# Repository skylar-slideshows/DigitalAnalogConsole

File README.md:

Skylar - Digital/Analog Music Mixing Console / Gear
A music mixing console with a fully analog audio signal path (no DSP), managed by a digital control system.

The problem to fix
Historically, music recording studios relied on analog audio processing equipment. While digital signal processing has largely replaced it, many professional audio engineers still prefer analog hardware for its perceived superior sound quality. However, analog equipment lacks instant recall, requiring engineers to manually reset knobs and controls between projects. Since these knobs control actual resistances/potentiometers in the signal path, they need to be physically moved to the right place. In today's fast-paced production environment, where multiple sessions may be completed in a single day, this process can be time-consuming and impractical.

Proposal
My proposal is to design a set of basic audio engineering analog sound processors (an EQualizer, a dynamic range compressor, and volume control) with a digital system that uses “voltage controlled resistors” to allow recall to be handled by a microprocessor, making it instant. Instead of having moving knobs that are physical resistors, the knobs will only be digital rotary encoders for which a microcontroller calculates their relative position. The microcontroller then uses a control voltage to set resistors in the analog signal path to the value that a real knob in that position would be, making the signal path exactly the same “to the audio.” This would also allow the microprocessor to automate and adjust many parameters at once, which is another limitation with analog audio equipment. These three basic devices can be combined into one digitally controlled, analog “channel strip” that handles one layer of audio in the mix of a song. Many of these channels side by side, with a master section that combines all the signals, makes an audio console. This kind of technology is present in some standalone pieces of audio equipment, as well as parts of some synthesizers, but it has never been done at such a large scale.

Technical explanation
The “knobs” in our device (actually rotary encoders), send a digital signal with their relative position. To “scan” all the digital encoder “knobs” positions’, a microcontroller can be multiplexed to them, cycling through looking at all the knobs’ data outputs several times per second, meaning a few GPIO pins can be used to interface with many knobs. 

The microcontroller then calculates the value that a real potentiometer (based on its value and taper - linear? Log? anti-log?) would have in that same positon.

To make voltage controlled resistors that actually supply this resistance in the analog audio path, there are many approaches. A FET transistor has a “triode” or “OHMIC” region between when it is on and off, of high resistance, which varies by its gate voltage. As long as we stay away from the very edges of this region, the behavior is approximately linear (moreso on JFETs - Junction Field Effect Transistors) making them suitable for audio.
Another way is with OTAs (operational transconductance amplifiers), which are voltage controlled current sources. Since resistors themselves turn voltage into current, OTAs are essentially like resistors for our purpose.

For a non-continuous controllable resistor, we can use a network of many resistors in series and parallel, with transistors (electronic switches) between them to connect them in various ways that can produce an equivalent resistance through the entire network of essentially any value we want. There are premade chips for this. (resistor ladders)

We need to make sure that however we control the components, it does not get in the way of making a highly linear (low harmonic distortion), high fidelity (flat frequency response between 20Hz and 20kHz) audio path - i.e. making a good sounding piece of equipment that doesn’t distort the sound.

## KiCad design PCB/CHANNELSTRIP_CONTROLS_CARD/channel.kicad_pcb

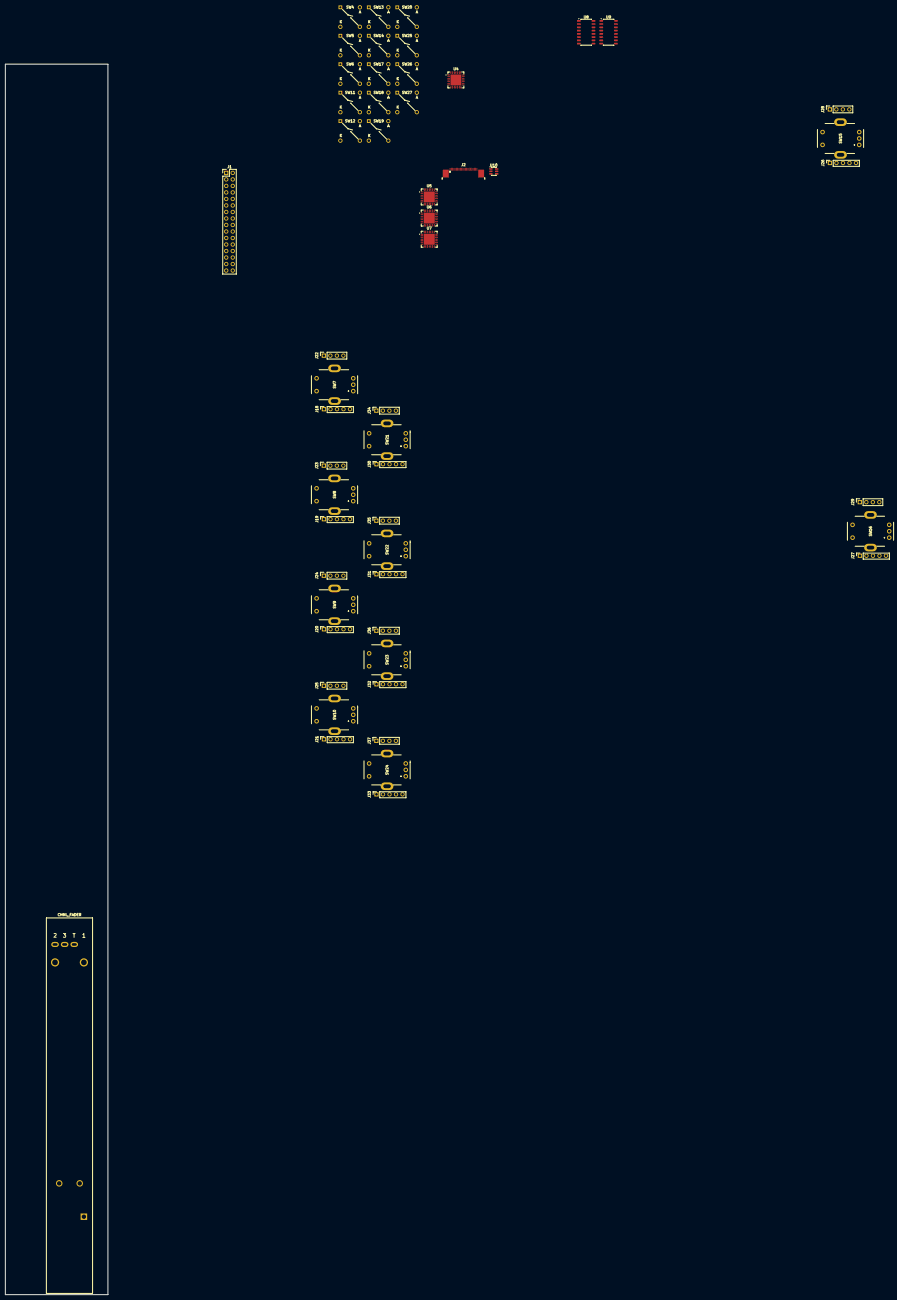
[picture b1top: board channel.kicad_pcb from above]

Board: 2 copper layers, 40.0 x 480.0 mm, 54 parts (0 on the bottom side), 80 nets, no tracks yet.

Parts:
F1: CHNL_FADER; TRIM_RSA0N11M9A07
J1: CONN; PinHeader_2x16_P2.54mm_Vertical
J2: SCREEN; TE_2-1734839-2_1x22-1MP_P0.5mm_Horizontal
J18, J19, J20, J21, J26, J27, J30, J31, J32, J33: KNOB_LED_D1; PinSocket_1x05_P2.54mm_Vertical
J22, J23, J24, J25, J28, J29, J34, J35, J36, J37: KNOB_LED_P1; PinSocket_1x04_P2.54mm_Vertical
SW4: MIC; CFPB-1CC-4W6
SW5: V48; CFPB-1CC-4W6
SW6: EQ; CFPB-1CC-4W6
SW7: KNOB_CTRL_1A; EC11J0924411
SW8: KNOB_CTRL_2A; EC11J0924411
SW9: KNOB_CTRL_3A; EC11J0924411
SW10: KNOB_CTRL_4A; EC11J0924411
SW11: LINE; CFPB-1CC-4W6
SW12: PHASE; CFPB-1CC-4W6
SW13: COMP; CFPB-1CC-4W6
SW14: SOLO; CFPB-1CC-4W6
SW15: KNOB_INPUT; EC11J0924411
SW16: KNOB_PAN; EC11J0924411
SW17: HIZ; CFPB-1CC-4W6
SW18: HPF; CFPB-1CC-4W6
SW19: SEND; CFPB-1CC-4W6
SW20: MUTE; CFPB-1CC-4W6
SW21: KNOB_CTRL_1B; EC11J0924411
SW22: KNOB_CTRL_2B; EC11J0924411
SW23: KNOB_CTRL_3B; EC11J0924411
SW24: KNOB_CTRL_4B; EC11J0924411
SW25: INS; CFPB-1CC-4W6
SW26: PRE; CFPB-1CC-4W6
SW27: SEL; CFPB-1CC-4W6
U4, U5, U6, U7: MCP23017x-x-ML; QFN-28-1EP_6x6mm_P0.65mm_EP4.25x4.25mm
U8, U9: 74HCT595D; JEITA_SOIC-16_3.9x9.9mm_P1.27mm
U10: TTP223-BA6; SOT-23-6

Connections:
+2V8: J1.10, J1.12, J2.3, J2.4, J2.6
+3.3V: J1.2, J1.4, U4.5 (V_{DD}), U4.14 (~RESET), U5.5 (V_{DD}), U5.11 (A0), U5.14 (~RESET), U6.5 (V_{DD}), U6.12 (A1), U6.14 (~RESET), U7.5 (V_{DD}), U7.11 (A0), U7.12 (A1), U7.14 (~RESET), U10.5 (VDD)
+3.3VA: F1.1, J1.30
+5V: J1.1, J1.3, J1.5, J22.3, J22.4, J23.3, J23.4, J24.3, J24.4, J25.3, J25.4, J28.3, J28.4, J29.3, J29.4, J34.3, J34.4, J35.3, J35.4, J36.3, J36.4, J37.3, J37.4, U8.16 (VCC), U9.16 (VCC)
+10V: J1.6, J1.8
/A1: SW4.2, U4.17 (GPA0)
/A2: SW11.2, U4.18 (GPA1)
/A3: SW17.2, U4.19 (GPA2)
/A4: SW5.2, U4.20 (GPA3)
/A5: SW12.2, U4.21 (GPA4)
/A6: SW18.2, U4.22 (GPA5)
/A7: SW6.2, U4.23 (GPA6)
/A8: SW13.2, U4.25 (GPB0)
/A9: SW19.2, U4.26 (GPB1)
/A10: SW14.2, U4.27 (GPB2)
/A11: SW20.2, U4.28 (GPB3)
/A12: SW27.2, U4.1 (GPB4)
/A13: SW25.2, U4.2 (GPB5)
/A14: SW26.2, U4.3 (GPB6)
/K1A: SW15.A (Pin_1), U5.17 (GPA0)
/K1B: SW15.B (Pin_3), U5.18 (GPA1)
/K1S: SW15.D (Pin_4), U5.19 (GPA2)
/K2A: SW7.A (Pin_1), U5.20 (GPA3)
/K2B: SW7.B (Pin_3), U5.21 (GPA4)
/K2S: SW7.D (Pin_4), U5.22 (GPA5)
/K3A: SW21.A (Pin_1), U5.23 (GPA6)
/K3B: SW21.B (Pin_3), U5.25 (GPB0)
/K3S: SW21.D (Pin_4), U5.26 (GPB1)
/K4A: SW8.A (Pin_1), U5.27 (GPB2)
/K4B: SW8.B (Pin_3), U5.28 (GPB3)
/K4S: SW8.D (Pin_4), U5.1 (GPB4)
/K5A: SW22.A (Pin_1), U5.2 (GPB5)
/K5B: SW22.B (Pin_3), U5.3 (GPB6)
/K6A: SW9.A (Pin_1), U6.17 (GPA0)
/K6B: SW9.B (Pin_3), U6.18 (GPA1)
/K6S: SW9.D (Pin_4), U6.19 (GPA2)
/K7A: SW23.A (Pin_1), U6.20 (GPA3)
/K7B: SW23.B (Pin_3), U6.21 (GPA4)
/K8A: SW10.A (Pin_1), U6.22 (GPA5)
/K8B: SW10.B (Pin_3), U6.23 (GPA6)
/K8S: SW10.D (Pin_4), U6.25 (GPB0)
/K9A: SW24.A (Pin_1), U6.26 (GPB1)
/K9B: SW24.B (Pin_3), U6.27 (GPB2)
/K9S: SW24.D (Pin_4), U6.28 (GPB3), U7.17 (GPA0)
/K10A: SW16.A (Pin_1), U6.1 (GPB4), U7.18 (GPA1)
/K10B: SW16.B (Pin_3), U6.2 (GPB5), U7.19 (GPA2)
/K10S: SW16.D (Pin_4), U6.3 (GPB6), U7.20 (GPA3)
ADDR_MSB: J1.7, U4.13 (A2), U5.13 (A2), U6.13 (A2), U7.13 (A2)
DISP_A0: J1.28, J2.16
DISP_BRIGHT_PWM: J1.16, J2.1
DISP_CS: J1.26, J2.18
DISP_RST: J1.22, J2.20
DISP_SPI_CL: J1.20, J2.17
DISP_SPI_MOSI: J1.18, J2.21
DISP_TE: J1.24, J2.19
FADER_ADC: F1.2, J1.25
FADER_TOUCH: J1.27, U10.1 (Q)
GND: J1.9, J1.11, J2.2, J2.5, J2.7, J2.8, J2.9, J2.10, J2.11, J2.12, J2.13, J2.14, J2.15, J2.22, J2.MP (MountPin), J22.1, J22.2, J23.1, J23.2, J24.1, J24.2, J25.1, J25.2, J28.1, J28.2, J29.1, J29.2, J34.1, J34.2, J35.1, J35.2, J36.1, J36.2, J37.1, J37.2, SW4.1, SW4.4 (K), SW5.1, SW5.4 (K), SW6.1, SW6.4 (K), SW7.C (Pin_2), SW7.E (Pin_5), SW7.G (Pin_6), SW8.C (Pin_2), SW8.E (Pin_5), SW8.G (Pin_6), SW9.C (Pin_2), SW9.E (Pin_5), SW9.G (Pin_6), SW10.C (Pin_2), SW10.E (Pin_5), SW10.G (Pin_6), SW11.1, SW11.4 (K), SW12.1, SW12.4 (K), SW13.1, SW13.4 (K), SW14.1, SW14.4 (K), SW15.C (Pin_2), SW15.E (Pin_5), SW15.G (Pin_6), SW16.C (Pin_2), SW16.E (Pin_5), SW16.G (Pin_6), SW17.1, SW17.4 (K), SW18.1, SW18.4 (K), SW19.1, SW19.4 (K), SW20.1, SW20.4 (K), SW21.C (Pin_2), SW21.E (Pin_5), SW21.G (Pin_6), SW22.C (Pin_2), SW22.E (Pin_5), SW22.G (Pin_6), SW23.C (Pin_2), SW23.E (Pin_5), SW23.G (Pin_6), SW24.C (Pin_2), SW24.E (Pin_5), SW24.G (Pin_6), SW25.1, SW25.4 (K), SW26.1, SW26.4 (K), SW27.1, SW27.4 (K), U4.6 (V_{SS}), U4.11 (A0), U4.12 (A1), U4.29 (EP), U5.6 (V_{SS}), U5.12 (A1), U5.29 (EP), U6.6 (V_{SS}), U6.11 (A0), U6.29 (EP), U7.6 (V_{SS}), U7.29 (EP), U8.8 (GND), U8.10 (~SRCLR), U9.8 (GND), U9.10 (~SRCLR), U10.2 (VSS), U10.4 (AHLB), U10.6 (TOG)
GNDA: F1.3, J1.32
KNOB_I2C_CL: J1.23, U4.8 (SCK), U5.8 (SCK), U6.8 (SCK), U7.8 (SCK)
KNOB_I2C_DA: J1.21, U4.9 (SDA), U5.9 (SDA), U6.9 (SDA), U7.9 (SDA)
LED_BRIGHT_PWM: J1.19, J18.4, J19.4, J20.4, J21.4, J26.4, J27.4, J30.4, J31.4, J32.4, J33.4, U8.13 (~OE), U9.13 (~OE)
LED_CL: J1.15, J18.2, J19.2, J20.2, J21.2, J26.2, J27.2, J30.2, J31.2, J32.2, J33.2, U8.11 (SRCLK), U9.11 (SRCLK)
LED_DA: J1.13, J26.1
LED_LATCH: J1.17, J18.3, J19.3, J20.3, J21.3, J26.3, J27.3, J30.3, J31.3, J32.3, J33.3, U8.12 (RCLK), U9.12 (RCLK)
MOT_A_DIR: F1.A (Pin_5), J1.29
MOT_B_DIR: F1.B (Pin_6), J1.31
unnamed: F1.T (Pin_4), U10.3 (I)
unnamed: J18.1, J26.5
unnamed: J18.5, J30.1
unnamed: J19.1, J30.5
unnamed: J19.5, J31.1
unnamed: J20.1, J31.5
unnamed: J20.5, J32.1
unnamed: J21.1, J32.5
unnamed: J21.5, J33.1
unnamed: J27.1, J33.5
unnamed: J27.5, U8.14 (SER)
unnamed: U8.9 (QH'), U9.14 (SER)
OUT_LED_CAS: J1.14, U9.9 (QH')

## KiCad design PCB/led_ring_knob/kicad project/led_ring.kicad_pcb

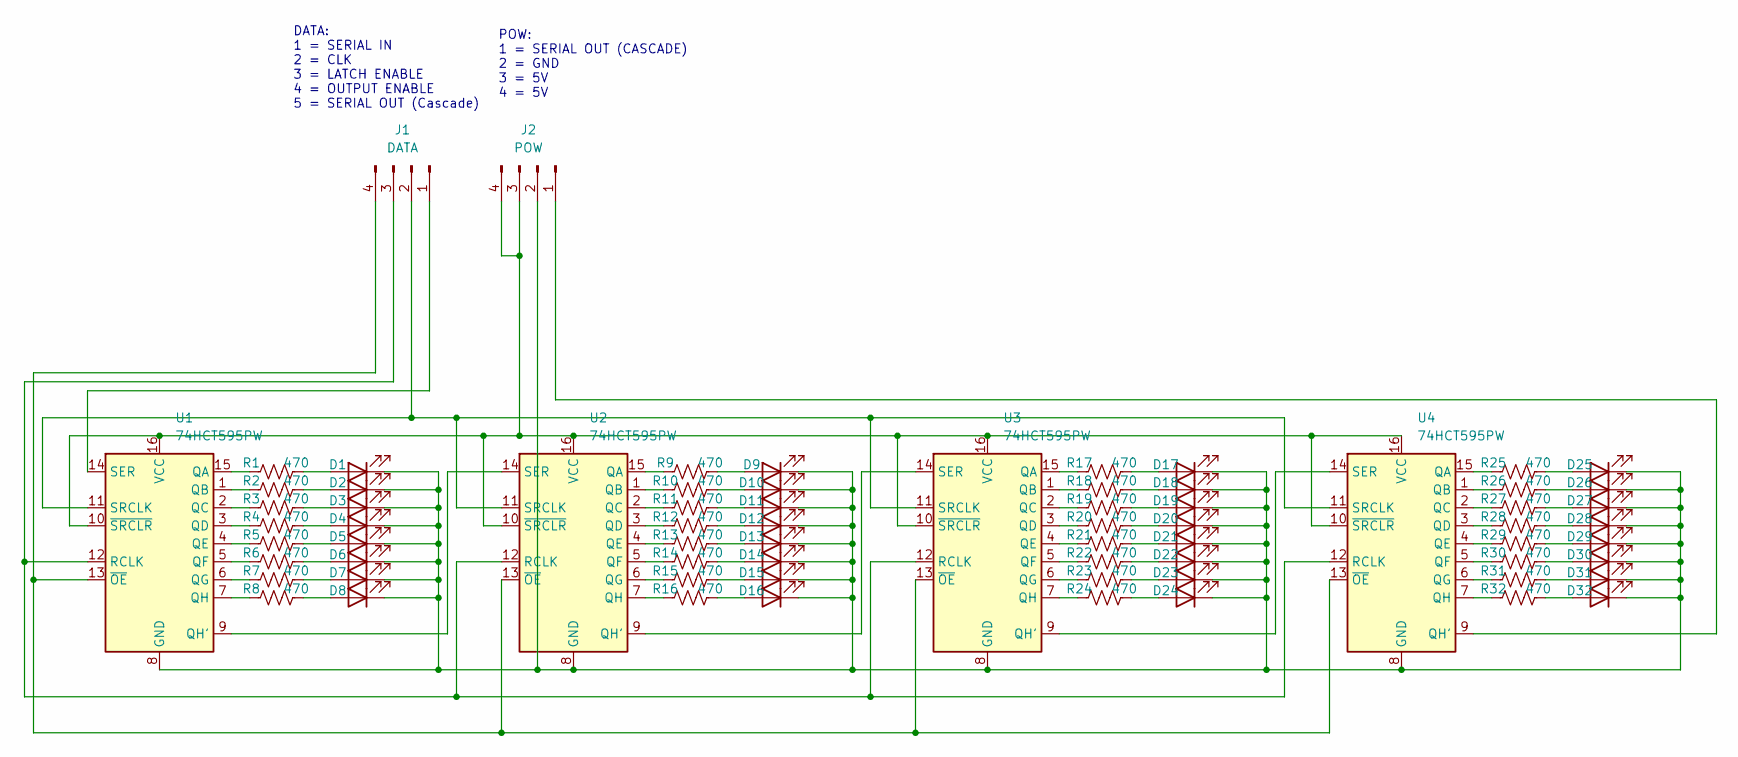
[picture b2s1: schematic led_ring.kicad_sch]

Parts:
D1, D2, D3, D4, D5, D6, D7, D8, D9, D10, D11, D12, D13, D14, D15, D16, D17, D18, D19, D20, D21, D22, D23, D24, D25, D26, D27, D28, D29, D30, D31, D32: CSP0603AN101-WP30300563001-3T; LED_0201_0603Metric; LCSC C52675959
J1: DATA; PinHeader_1x04_P2.54mm_Vertical; LCSC C5116483
J2: POW; PinHeader_1x04_P2.54mm_Vertical; LCSC C5116483
R1, R2, R3, R4, R5, R6, R7, R8, R9, R10, R11, R12, R13, R14, R15, R16, R17, R18, R19, R20, R21, R22, R23, R24, R25, R26, R27, R28, R29, R30, R31, R32: 470; R_0201_0603Metric; LCSC C295802
U1, U2, U3, U4: 74HCT595PW; TSSOP-16_4.4x5mm_P0.65mm; LCSC C54411086

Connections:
unnamed: D1.2 (A), R1.2
unnamed: D1.1 (K), D2.1 (K), D3.1 (K), D4.1 (K), D5.1 (K), D6.1 (K), D7.1 (K), D8.1 (K), D9.1 (K), D10.1 (K), D11.1 (K), D12.1 (K), D13.1 (K), D14.1 (K), D15.1 (K), D16.1 (K), D17.1 (K), D18.1 (K), D19.1 (K), D20.1 (K), D21.1 (K), D22.1 (K), D23.1 (K), D24.1 (K), D25.1 (K), D26.1 (K), D27.1 (K), D28.1 (K), D29.1 (K), D30.1 (K), D31.1 (K), D32.1 (K), J2.2, U1.8 (GND), U2.8 (GND), U3.8 (GND), U4.8 (GND)
unnamed: D2.2 (A), R2.2
unnamed: D3.2 (A), R3.2
unnamed: D4.2 (A), R4.2
unnamed: D5.2 (A), R5.2
unnamed: D6.2 (A), R6.2
unnamed: D7.2 (A), R7.2
unnamed: D8.2 (A), R8.2
unnamed: D9.2 (A), R9.2
unnamed: D10.2 (A), R10.2
unnamed: D11.2 (A), R11.2
unnamed: D12.2 (A), R12.2
unnamed: D13.2 (A), R13.2
unnamed: D14.2 (A), R14.2
unnamed: D15.2 (A), R15.2
unnamed: D16.2 (A), R16.2
unnamed: D17.2 (A), R17.2
unnamed: D18.2 (A), R18.2
unnamed: D19.2 (A), R19.2
unnamed: D20.2 (A), R20.2
unnamed: D21.2 (A), R21.2
unnamed: D22.2 (A), R22.2
unnamed: D23.2 (A), R23.2
unnamed: D24.2 (A), R24.2
unnamed: D25.2 (A), R25.2
unnamed: D26.2 (A), R26.2
unnamed: D27.2 (A), R27.2
unnamed: D28.2 (A), R28.2
unnamed: D29.2 (A), R29.2
unnamed: D30.2 (A), R30.2
unnamed: D31.2 (A), R31.2
unnamed: D32.2 (A), R32.2
unnamed: J1.1, U1.14 (SER)
unnamed: J1.2, U1.11 (SRCLK), U2.11 (SRCLK), U3.11 (SRCLK), U4.11 (SRCLK)
unnamed: J1.3, U1.12 (RCLK), U2.12 (RCLK), U3.12 (RCLK), U4.12 (RCLK)
unnamed: J1.4, U1.13 (~OE), U2.13 (~OE), U3.13 (~OE), U4.13 (~OE)
unnamed: J2.1, U4.9 (QH')
unnamed: J2.3, J2.4, U1.10 (~SRCLR), U1.16 (VCC), U2.10 (~SRCLR), U2.16 (VCC), U3.10 (~SRCLR), U3.16 (VCC), U4.10 (~SRCLR), U4.16 (VCC)
unnamed: R1.1, U1.15 (QA)
unnamed: R2.1, U1.1 (QB)
unnamed: R3.1, U1.2 (QC)
unnamed: R4.1, U1.3 (QD)
unnamed: R5.1, U1.4 (QE)
unnamed: R6.1, U1.5 (QF)
unnamed: R7.1, U1.6 (QG)
unnamed: U1.9 (QH'), U2.14 (SER)
unnamed: R8.1, U1.7 (QH)
unnamed: R9.1, U2.15 (QA)
unnamed: R10.1, U2.1 (QB)
unnamed: R11.1, U2.2 (QC)
unnamed: R12.1, U2.3 (QD)
unnamed: R13.1, U2.4 (QE)
unnamed: R14.1, U2.5 (QF)
unnamed: R15.1, U2.6 (QG)
unnamed: U2.9 (QH'), U3.14 (SER)
unnamed: R16.1, U2.7 (QH)
unnamed: R17.1, U3.15 (QA)
unnamed: R18.1, U3.1 (QB)
unnamed: R19.1, U3.2 (QC)
unnamed: R20.1, U3.3 (QD)
unnamed: R21.1, U3.4 (QE)
unnamed: R22.1, U3.5 (QF)
unnamed: R23.1, U3.6 (QG)
unnamed: U3.9 (QH'), U4.14 (SER)
unnamed: R24.1, U3.7 (QH)
unnamed: R25.1, U4.15 (QA)
unnamed: R26.1, U4.1 (QB)
unnamed: R27.1, U4.2 (QC)
unnamed: R28.1, U4.3 (QD)
unnamed: R29.1, U4.4 (QE)
unnamed: R30.1, U4.5 (QF)
unnamed: R31.1, U4.6 (QG)
unnamed: R32.1, U4.7 (QH)

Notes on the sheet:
DATA: 1 = SERIAL IN 2 = CLK 3 = LATCH ENABLE 4 = OUTPUT ENABLE 5 = SERIAL OUT (Cascade)
POW: 1 = SERIAL OUT (CASCADE) 2 = GND 3 = 5V 4 = 5V

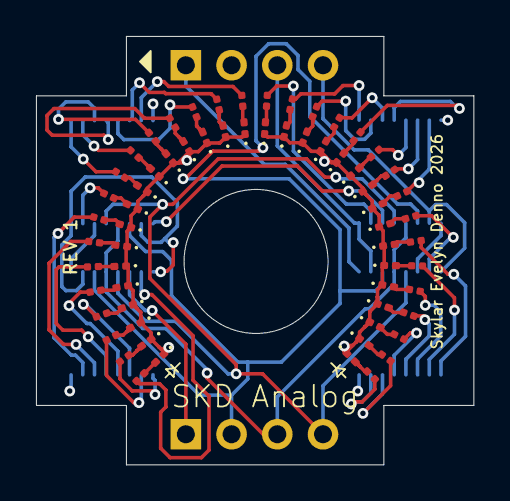
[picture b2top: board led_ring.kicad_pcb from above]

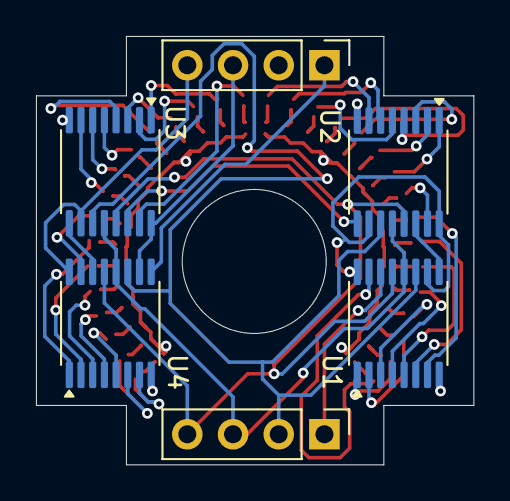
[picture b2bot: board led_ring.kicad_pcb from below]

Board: 4 copper layers, 24.3 x 23.8 mm, 70 parts (6 on the bottom side), 74 nets.

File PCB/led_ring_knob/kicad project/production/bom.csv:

Designator,Footprint,Quantity,Value,LCSC Part #
"D1, D10, D11, D12, D13, D14, D15, D16, D17, D18, D19, D2, D20, D21, D22, D23, D24, D25, D26, D27, D28, D29, D3, D30, D31, D32, D4, D5, D6, D7, D8, D9",0201,32,CSP0603AN101-WP30300563001-3T,C52675959
J1,PinHeader_1x04_P2.54mm_Vertical,1,DATA,C5116483
J2,PinHeader_1x04_P2.54mm_Vertical,1,POW,C5116483
"R1, R10, R11, R12, R13, R14, R15, R16, R17, R18, R19, R2, R20, R21, R22, R23, R24, R25, R26, R27, R28, R29, R3, R30, R31, R32, R4, R5, R6, R7, R8, R9",0201,32,470,C295802
"U1, U2, U3, U4",TSSOP-16_4.4x5mm_P0.65mm,4,74HCT595PW,C54411086

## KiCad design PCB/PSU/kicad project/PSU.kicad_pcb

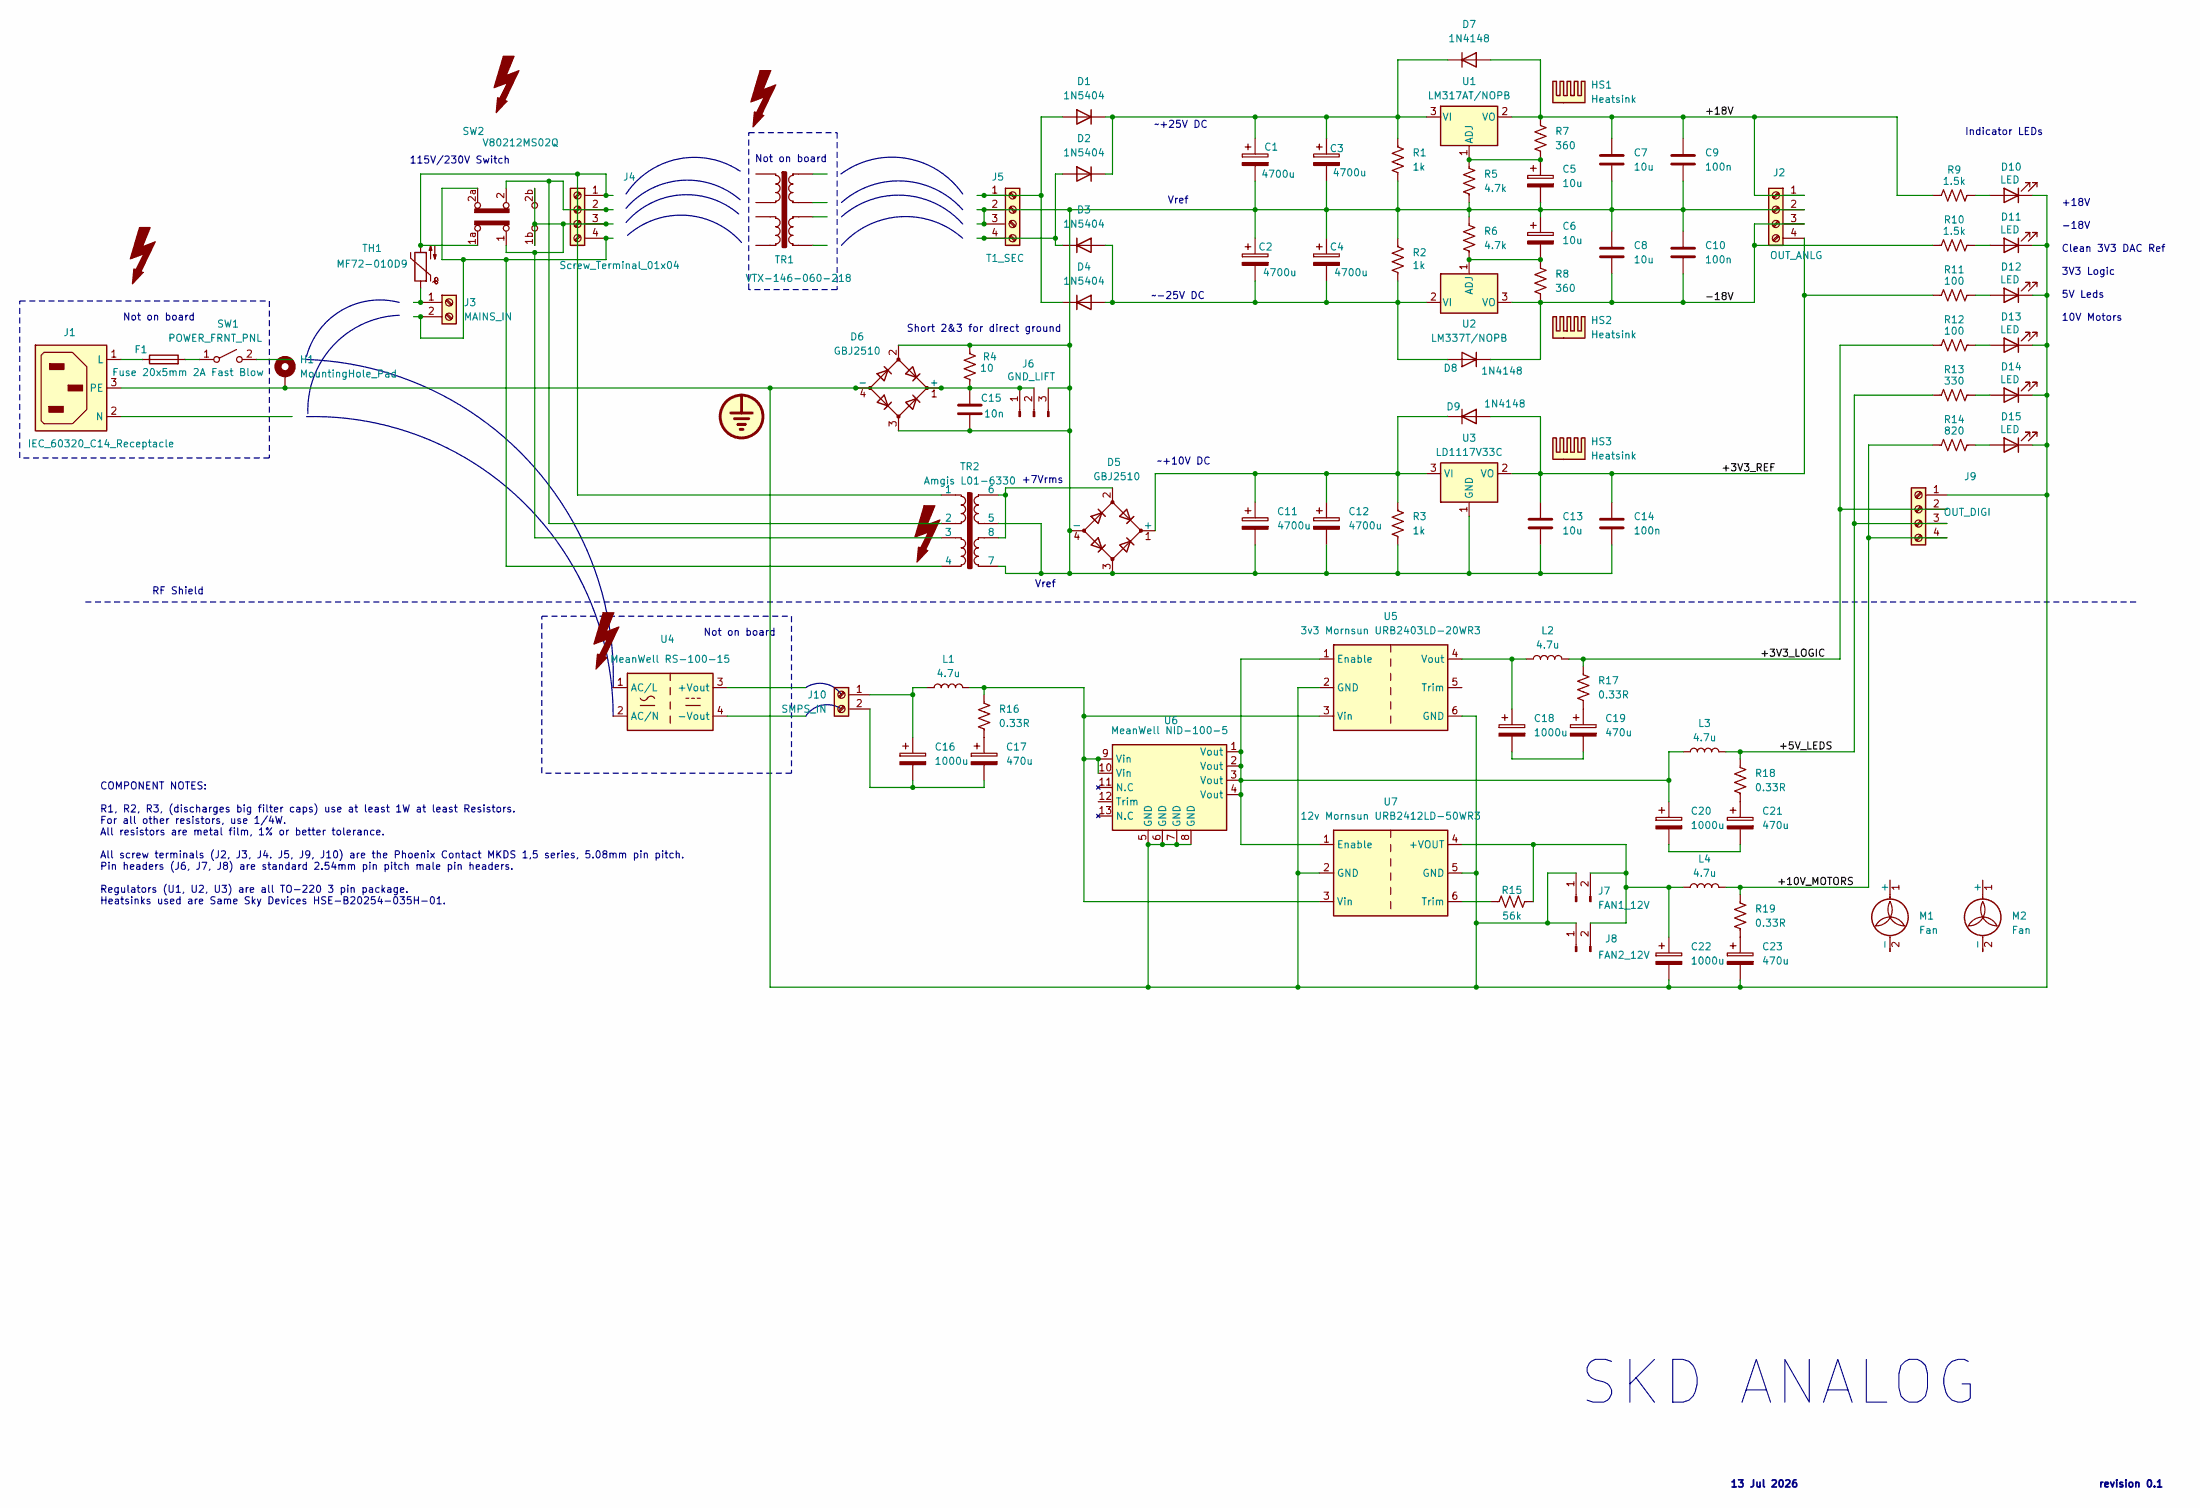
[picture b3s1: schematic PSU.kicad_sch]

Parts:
C1, C2, C3, C4, C11, C12: 4700u; CP_Radial_D18.0mm_P7.50mm; LCSC C443892
C5, C6: 10u; CP_Elec_6.3x5.4; LCSC C14162
C7, C8, C13: 10u; C_Rect_L24.0mm_W12.6mm_P22.50mm_MKT; LCSC C328801
C9, C10, C14: 100n; C_1206_3216Metric; LCSC C1945
C15: 10n; C_1206_3216Metric; LCSC C55077
C16, C18, C20, C22: 1000u; CP_Radial_D12.5mm_P5.00mm; LCSC C122661
C17, C19, C21, C23: 470u; CP_Radial_D10.0mm_P5.00mm; LCSC C116237
D1, D2, D3, D4: 1N5404; D_DO-201AD_P15.24mm_Horizontal; LCSC C222547
D5, D6: GBJ2510; Diode_Bridge_32.0x5.6x17.0mm_P10.0mm_P7.5mm; LCSC C27523
D7, D8, D9: 1N4148; D_SOD-123; LCSC C2099
D10, D11, D12, D13, D14, D15: LED; LED_Rectangular_W3.9mm_H1.8mm
F1: Fuse 20x5mm 2A Fast Blow
H1: MountingHole_Pad; MountingHole_3.2mm_M3_Pad_TopBottom
HS1, HS2, HS3: Heatsink; HSINK_HSE-B20380-040H
J1: IEC_60320_C14_Receptacle
J2: OUT_ANLG; TerminalBlock_Phoenix_MKDS-1,5-4-5.08_1x04_P5.08mm_Horizont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; LCSC C5443561
J3: MAINS_IN; TerminalBlock_Phoenix_MKDS-1,5-2-5.08_1x02_P5.08mm_Horizont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; LCSC C5443539
J4: Screw_Terminal_01x04; TerminalBlock_Phoenix_MKDS-1,5-4-5.08_1x04_P5.08mm_Horizont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; LCSC C5443561
J5: T1_SEC; TerminalBlock_Phoenix_MKDS-1,5-4_1x04_P5.00mm_Horizontal; LCSC C5443561
J6: GND_LIFT; PinHeader_1x03_P2.54mm_Vertical; LCSC C5360899
J7: FAN1_12V; PinHeader_1x02_P2.54mm_Vertical; LCSC C5360898
J8: FAN2_12V; PinHeader_1x02_P2.54mm_Vertical; LCSC C5360898
J9: OUT_DIGI; TerminalBlock_Phoenix_MKDS-1,5-4-5.08_1x04_P5.08mm_Horizont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; LCSC C5443561
J10: SMPS_IN; TerminalBlock_Phoenix_MKDS-1,5-2-5.08_1x02_P5.08mm_Horizont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; LCSC C5443539
L1, L2, L3, L4: 4.7u; L_Vishay_IHLP-5050; LCSC C845092
M1, M2: Fan
R1, R2, R3: 1k; R_Axial_DIN0414_L11.9mm_D4.5mm_P20.32mm_Horizontal; LCSC C5200473
R4: 10; R_0805_2012Metric; LCSC C340448
R5, R6: 4.7k; R_1206_3216Metric; LCSC C702850
R7, R8: 360; R_1206_3216Metric; LCSC C497314
R9, R10: 1.5k; R_1206_3216Metric; LCSC C26030
R11, R12: 100; R_1206_3216Metric; LCSC C49286685
R13: 330; R_1206_3216Metric; LCSC C49330184
R14: 820; R_1206_3216Metric; LCSC C17984
R15: 56k; R_1206_3216Metric; LCSC C4513
R16, R17, R18, R19: 0.33R; R_Axial_DIN0207_L6.3mm_D2.5mm_P10.16mm_Horizontal; LCSC C119970
SW1: POWER_FRNT_PNL
SW2: V80212MS02Q; SW_V80214MS02Q
TH1: MF72-010D9; C_Disc_D12.5mm_W5.0mm_P7.50mm
TR1: VTX-146-060-218
TR2: Amgis L01-6330; AMGIS L01-63XX
U1: LM317AT/NOPB; TO-220-3_Vertical; LCSC C94659
U2: LM337T/NOPB; TO-220-3_Vertical; LCSC C2869423
U3: LD1117V33C; TO-220-3_Vertical; LCSC C672117
U4: MeanWell RS-100-15
U5: 3v3 Mornsun URB2403LD-20WR3; Converter_DCDC_XP_POWER_JTDxxxxxxx_THT
U6: MeanWell NID-100-5; MeanWell NID100
U7: 12v Mornsun URB2412LD-50WR3; urb 50w dc-dc

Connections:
/+3V3_LOGIC: J9.2, L2.2, R12.1, R17.1
/+3V3_REF: C13.1, C14.1, D9.2 (A), J2.4, R11.1, U3.2 (VO)
/+5V_LEDS: J9.3, L3.2, R13.1, R18.1
/+10V_MOTORS: J9.4, L4.2, R14.1, R19.1
/+18V: C7.1, C9.1, D7.2 (A), J2.1, R7.1, R9.1, U1.2 (VO)
/-18V: C8.2, C10.2, D8.1 (K), J2.3, R8.2, R10.1, U2.3 (VO)
unnamed: C17.1, R16.2
unnamed: C18.2, C19.2
unnamed: C19.1, R17.2
unnamed: C20.2, C21.2
unnamed: C21.1, R18.2
unnamed: C23.1, R19.2
unnamed: D1.2 (A), D4.1 (K), J5.1
unnamed: C1.1, C3.1, D1.1 (K), D2.1 (K), D7.1 (K), R1.1, U1.3 (VI)
unnamed: D2.2 (A), D3.1 (K), J5.4
unnamed: C2.2, C4.2, D3.2 (A), D4.2 (A), D8.2 (A), R2.2, U2.2 (VI)
unnamed: C11.1, C12.1, D5.1 (+), D9.1 (K), R3.1, U3.3 (VI)
unnamed: C1.2, C2.1, C3.2, C4.1, C5.2, C6.1, C7.2, C8.1, C9.2, C10.1, C11.2, C12.2, C13.2, C14.2, C15.1, D5.3, D5.4 (-), D6.2, D6.3, J2.2, J5.2, J5.3, J6.3, R1.2, R2.1, R3.2, R4.2, R5.2, R6.1, TR2.5, TR2.7, U3.1 (GND)
unnamed: D5.2, TR2.6, TR2.8
unnamed: D10.2 (A), R9.2
unnamed: C15.2, C22.2, C23.2, D6.1 (+), D6.4 (-), D10.1 (K), D11.1 (K), D12.1 (K), D13.1 (K), D14.1 (K), D15.1 (K), H1.1 (1_1), J1.3 (PE), J6.1, J6.2, J7.1, J8.1, J9.1, R4.1, U5.2 (GND), U5.6 (GND), U6.5 (GND), U6.6 (GND), U6.7 (GND), U6.8 (GND), U7.2 (GND), U7.5 (GND)
unnamed: D11.2 (A), R10.2
unnamed: D12.2 (A), R11.2
unnamed: D13.2 (A), R12.2
unnamed: D14.2 (A), R13.2
unnamed: D15.2 (A), R14.2
unnamed: F1.1, J1.1 (L)
unnamed: F1.2, SW1.1 (A)
unnamed: J3.1, TH1.1
unnamed: J3.2, J4.4, SW2.2a, TR2.4
unnamed: J4.1, SW2.1a, TH1.2, TR2.1
unnamed: J4.2, SW2.2, TR2.2
unnamed: J4.3, SW2.1, SW2.1b, SW2.2b, TR2.3
unnamed: C22.1, J7.2, J8.2, L4.1, R15.2, U7.4 (+VOUT)
unnamed: C16.1, J10.1, L1.1
unnamed: C16.2, C17.2, J10.2
unnamed: C5.1, R5.1, R7.2, U1.1 (ADJ)
unnamed: C6.2, R6.2, R8.1, U2.1 (ADJ)
unnamed: C20.1, L3.1, U5.1 (Enable), U6.1 (Vout), U6.2 (Vout), U6.3 (Vout), U6.4 (Vout), U7.1 (Enable)
unnamed: L1.2, R16.1, U5.3 (Vin), U6.9 (Vin), U6.10 (Vin), U7.3 (Vin)
unnamed: C18.1, L2.1, U5.4 (Vout)
unnamed: R15.1, U7.6 (Trim)

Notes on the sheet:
Indicator LEDs
COMPONENT NOTES: R1, R2, R3, (discharges big filter caps) use at least 1W at least Resistors. For all other resistors, use 1/4W. All resistors are metal film, 1% or better tolerance. All screw terminals (J2, J3, J4. J5, J9, J10) are the Phoenix Contact MKDS 1,5 series, 5.08mm pin pitch. Pin headers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
Vref
Short 2&3 for direct ground
+7Vrms
~-25V DC
revision 0.1
~+10V DC
~+25V DC
+18V -18V Clean 3V3 DAC Ref 3V3 Logic 5V Leds 10V Motors
115V/230V Switch
Not on board
13 Jul 2026
RF Shield
SKD ANALOG

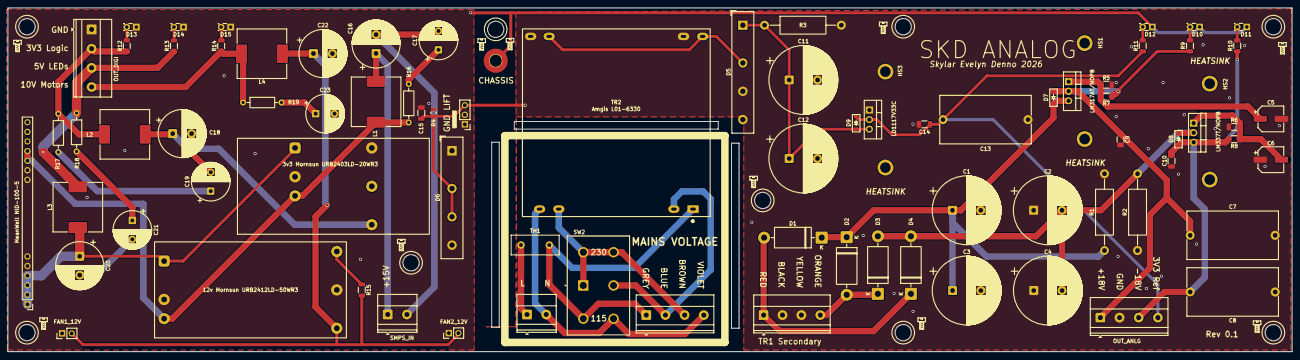
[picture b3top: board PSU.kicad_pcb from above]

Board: 4 copper layers, 340.0 x 91.0 mm, 83 parts (0 on the bottom side), 40 nets.

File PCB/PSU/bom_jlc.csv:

"Reference","Value","LCSC"
"C1,C2,C3,C4,C11,C12","4700u","C443892"
"C5,C6","10u","C14162"
"C7,C8,C13","10u","C328801"
"C9,C10,C14","100n","C1945"
"C15","10n","C55077"
"C16,C18,C20,C22","1000u","C122661"
"C17,C19,C21,C23","470u","C116237"
"D1,D2,D3,D4","1N5404","C222547"
"D5,D6","GBJ2510","C27523"
"D7,D8,D9","1N4148","C2099"
"J2,J4,J5,J9","OUT_ANLG,OUT_DIGI,Screw_Terminal_01x04,T1_SEC","C5443561"
"J3,J10","MAINS_IN,SMPS_IN","C5443539"
"J6","GND_LIFT","C5360899"
"J7,J8","FAN1_12V,FAN2_12V","C5360898"
"L1,L2,L3,L4","4.7u","C845092"
"R1,R2,R3","1k","C5200473"
"R4","10","C340448"
"R5,R6","4.7k","C702850"
"R7,R8","360","C497314"
"R9,R10","1.5k","C26030"
"R11,R12","100","C49286685"
"R13","330","C49330184"
"R14","820","C17984"
"R15","56k","C4513"
"R16,R17,R18,R19","0.33R","C119970"
"U1","LM317AT/NOPB","C94659"
"U2","LM337T/NOPB","C2869423"
"U3","LD1117V33C","C672117"
